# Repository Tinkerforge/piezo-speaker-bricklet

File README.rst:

Piezo Speaker Bricklet
======================

This repository contains the firmware source code and the hardware design
files. The documentation generator configs can be found at
https://github.com/Tinkerforge/generators

Repository Content
------------------

software/:
 * examples/: Examples for all supported languages
 * build/: Compiled files
 * src/: Source code of firmware
 * Makefile: Makefile to build project

hardware/:
 * Contains KiCad project files and additionally schematics as PDF

datasheets/:
 * Contains datasheets for sensors and complex ICs that are used

Hardware
--------

The hardware is designed with the open source EDA Suite KiCad
(http://www.kicad.org). Before you are able to open the files,
you have to install the Tinkerforge kicad-libraries
(https://github.com/Tinkerforge/kicad-libraries). You can either clone
them directly in hardware/ or clone them in a separate folder and
symlink them into hardware/
(ln -s kicad_path/kicad-libraries project_path/hardware). After that you
can open the .pro file in hardware/ with KiCad and from there view and
modify the schematics and the PCB layout.

Software
--------

If you want to do your own Brick/Bricklet firmware development we highly
recommend that you use our build environment setup script and read the
tutorial (https://www.tinkerforge.com/en/doc/Tutorials/Tutorial_Build_Environment/Tutorial.html).

To compile the C code we recommend you to install the newest GNU Arm Embedded
Toolchain (https://launchpad.net/gcc-arm-embedded/+download).
You also need to install bricklib (https://github.com/Tinkerforge/bricklib)
and brickletlib (https://github.com/Tinkerforge/brickletlib).

You can either clone it directly in software/src/ or clone it in a
separate folder and symlink it into software/src/
(ln -s bricklib_path/bricklib project_path/software/src/ and
ln -s brickletlib_path/brickletlib project_path/software/src/).
Finally make sure to have CMake installed
(http://www.cmake.org/cmake/resources/software.html).

After that you can build the firmware by invoking make in software/.
The firmware (.bin) can then be found in software/build/ and uploaded
with brickv (click button "Flashing" on start screen).

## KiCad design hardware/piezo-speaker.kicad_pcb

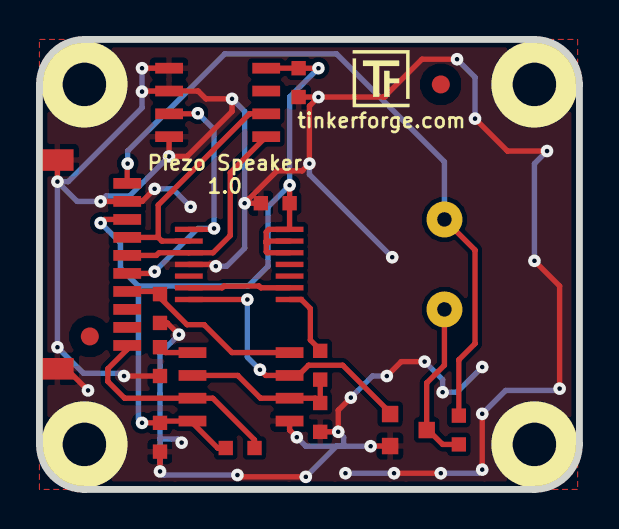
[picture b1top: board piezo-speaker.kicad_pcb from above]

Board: 2 copper layers, 30.0 x 25.0 mm, 23 parts (0 on the bottom side), 14 nets.

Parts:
C1, C2, C4: 100nF; C0603
C3: 5.6nF NC0; C0603
C5: 10nF; C0603
Fiducial_Mark: VAL**; Fiducial_Mark
Fiducial_Mark#2: VAL**; Fiducial_Mark
P1: CON-SENSOR
Q1: 2N7002P; SOT23GDS
R1, R3: 10k; R0603
R2: 18k; R0603
R4: 1k; R0603
SP1: PS1420
U1: M24C64; SOIC8
U2: MCP4651-104E/ST; TSSOP14
U3: ICM7555; SOIC8
U4, U5, U6, U7: DRILL; DRILL_NP
VAL: WEEE_7mm
VAL#2: CE_5mm

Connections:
+5V: P1.1, R4.1, SP1.1
Feedback: P1.10, R3.2, U3.7
GND: C1.2, C2.2, C3.1, C4.1, C5.1, P1.2, P1.EP, Q1.S, R1.2, U1.1, U1.2, U1.4, U2.4, U3.1
unnamed: C3.2, R2.2, U3.2, U3.6
unnamed: C5.2, U3.5
unnamed: P1.4, U1.6, U2.2
unnamed: P1.5, U1.5, U2.3
unnamed: P1.6, U1.3, U2.1
unnamed: Q1.D, R4.2, SP1.2
unnamed: U2.6, U2.9
POT1-A: R2.1, U2.8
POT2-A: Q1.G, U2.7, U3.3
Reset: P1.7, R1.1, U3.4
VCC: C1.1, C2.1, C4.2, P1.3, R3.1, U1.8, U2.12, U2.13, U2.14, U3.8

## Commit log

2013-08-23 Initial commit for Piezo Speaker Bricklet
2013-08-28 Add graph that shows relation between value and frequency
2013-08-28 Fix max frequency value for graph
2013-08-28 Change poti code to new poti configuration (two potis in series)
2013-08-30 value to frquency graph for new capacitor and resistor values
2013-09-04 Add frequency calibration function
2013-09-12 Add examples for Piezo Speaker Bricklet
2013-10-15 add hardware files
2013-10-18 add missing schematic
2013-12-09 Fix morse-code-overwrite bug
2014-01-10 Add Perl examples
2014-01-15 php: Use const for constant values
2014-02-07 Add Mathematica examples
2014-02-10 perl: fixed namespace
2014-02-12 javascript: add examples
2014-02-18 javascript: examples fixed
2014-02-20 javascript: add html exmaples
2014-02-24 javascript: port 4280, startExample()
2014-02-28 javascript: Break long lines and cleanup whitespace
2014-03-05 Add LabVIEW examples
2014-03-06 labview: Add examples in LV2010 format
2014-03-27 matlab: add examples
2014-04-02 java: Unify constants style
2014-04-02 perl: Unify print style
2014-04-17 Fix typos
2014-04-17 matlab: Add parentheses to make pygments happy
2014-07-15 java: Replace System.console() usage with an Eclipse compatible pattern
2014-08-19 Duration 0 stops beep, duration UINT32_MAX results in an infinite beep
2014-08-19 Update changelog
2014-12-02 Use ReadLine instead of ReadKey for C# example
2015-02-13 vbnet: Use ReadLine instead of ReadKey
    Because ReadKey doesn't work with a pipe as stdin on the RED Brick.
2015-03-02 windows: Stop cmake from searching for mingw32-make.exe
    Using MinGW Makefiles as generator makes cmake search for mingw32-make.exe
    which might not be installed because GnuWin32's make.exe is used instead.
2015-04-09 c: Whitespace
2015-04-09 python: Add missing disconnect calls
2015-07-25 Make JavaScript browser example textarea readonly
2015-07-27 Cleanup C/C++, C#, Java, Python and Ruby examples
2015-07-29 Reformat changelog
2015-08-07 Use full device class name in Python examples
2015-08-12 Fix minor warnings in C/C++ examples
2015-08-14 Cleanup Delphi examples
2015-08-18 Cleanup VB.NET examples
2015-08-19 Cleanup Perl examples
2015-09-09 Duplicate cmake call to fix bug during cmake creation
2015-09-23 Generator based example cleanup
2015-11-12 matlab: Fix callback handling for R2014a
    http://undocumentedmatlab.com/blog/matlab-callbacks-for-java-events-in-r2014a
2015-11-25 Include date and commit into changelog
2016-05-18 c: Add missing device destroy call
2016-07-01 Make the change UID comment more explicit
2017-06-02 octave: Use javaObject instead of deprecated java_new
2017-11-15 Add 3d information
2017-11-15 Fix edge cuts
2017-11-20 Add 3d model (*.step & *.FCStd)
2017-12-07 mathematica: Also generate .nb files
2018-02-19 javascript: Close div tag correctly
2018-02-20 Cleanup KiCad libraries config
    Ensure LibDir=kicad-libraries and LibName1=tinkerforge.
    Remove special library.
2018-05-11 Rename files
2018-05-24 perl: Use strict in examples
2018-07-11 Add Makefile with docker support
2018-07-11 Update directory structure and build instructions
2018-07-11 Remove obsolete generate_makefile scripts
2018-11-06 Add rust examples
2018-11-07 rust: Accept host names for ip connection, fix naming inconsistencies
2018-12-14 Add go examples.
2018-12-18 go: Change import path.
2018-12-18 go: Change import path again.
2018-12-20 rust: Reformat examples.
2019-01-24 mqtt: Add examples.
2019-01-24 mqtt: Fix example header.
2019-01-24 mqtt: Remove executable bit in example permissions.
2019-01-24 go: Minor example fixes.
2019-08-19 Don't disable IRQs during calibration
    Mewer Brick versions use interrupts during I2C communication
2019-08-19 Add rev for 2.0.3
2020-01-13 examples: Use python3 input instead of python2 raw_input.
2020-03-16 Whitespace
2020-04-07 examples: rust: Always block when calling bindings functions.
2021-10-25 Update KiCad link
    https://www.kicad.org/blog/2021/10/Avoid-links-to-former-kicad-domain/
2022-07-06 Add license files.

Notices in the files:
hardware/piezo-speaker.kicad_pcb:
Licensed under CERN OHL v.1.1
Copyright (©) 2013, B.Nordmeyer
Copyright Tinkerforge GmbH 2013.
This documentation describes Open Hardware and is licensed under the
CERN OHL v. 1.1.
